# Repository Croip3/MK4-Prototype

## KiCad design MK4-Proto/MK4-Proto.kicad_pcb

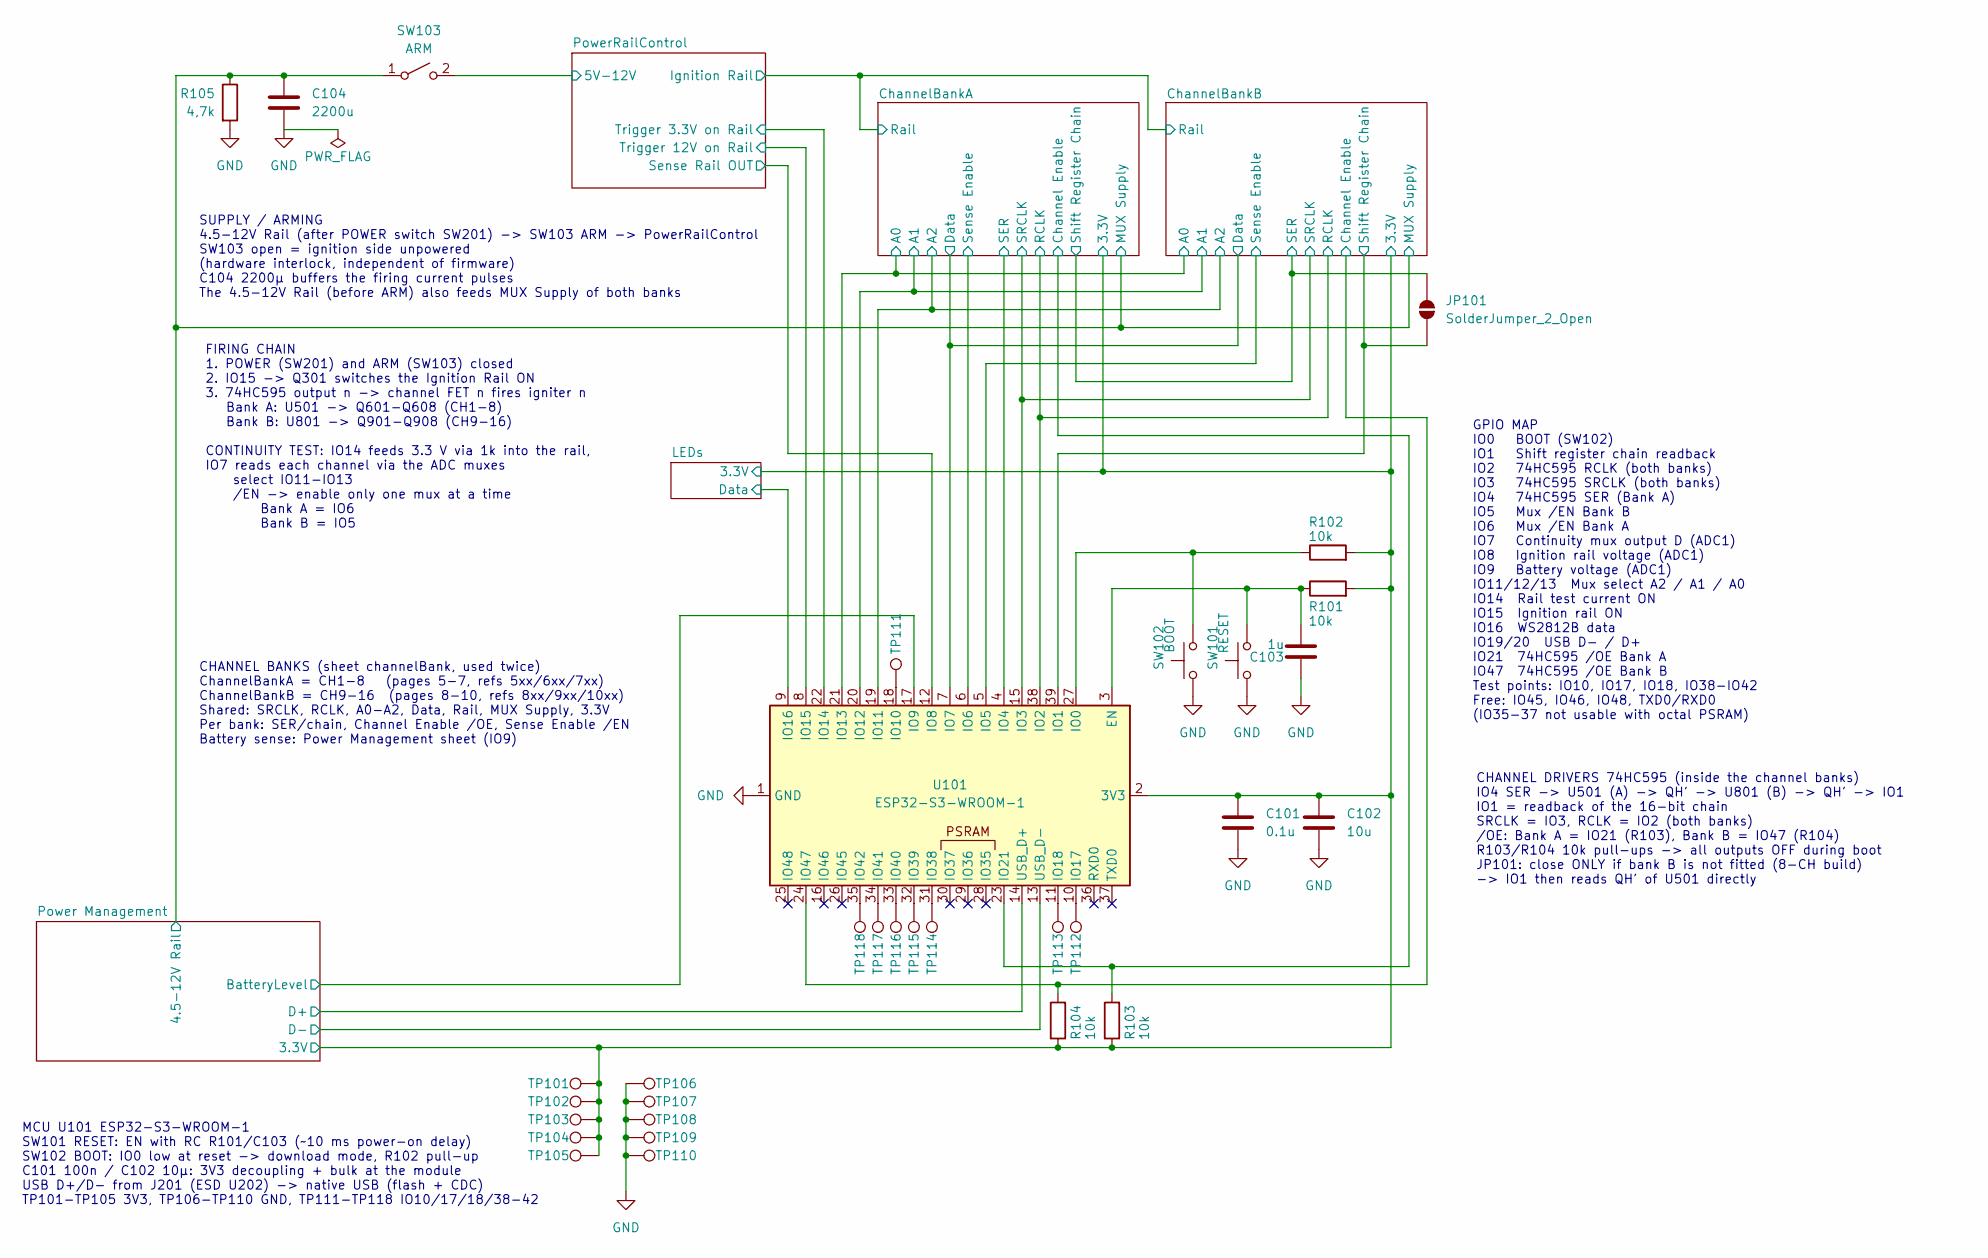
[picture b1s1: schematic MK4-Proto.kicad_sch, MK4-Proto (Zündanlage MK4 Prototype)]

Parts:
C101: 0.1u; C_0805_2012Metric_Pad1.18x1.45mm_HandSolder; LCSC C49678
C102: 10u; C_0805_2012Metric_Pad1.18x1.45mm_HandSolder; LCSC C15850
C103: 1u; C_0805_2012Metric_Pad1.18x1.45mm_HandSolder; LCSC C28323
C104: 2200u; CP_Elec_10x12.6; LCSC C48542923
JP101: SolderJumper_2_Open; SolderJumper-2_P1.3mm_Open_RoundedPad1.0x1.5mm
R101, R102, R103, R104: 10k; R_0603_1608Metric_Pad0.98x0.95mm_HandSolder; LCSC C25804
R105: 4,7k; R_0603_1608Metric_Pad0.98x0.95mm_HandSolder; LCSC C23162
SW101: RESET; SW_PUSH_6mm; LCSC C393938
SW102: BOOT; SW_PUSH_6mm; LCSC C393938
SW103: ARM; SolderWire-0.5sqmm_1x02_P4.6mm_D0.9mm_OD2.1mm
TP101, TP102, TP103, TP104, TP105: 3V3; TestPoint_THTPad_D2.0mm_Drill1.0mm
TP106, TP107, TP108, TP109, TP110: GND; TestPoint_THTPad_D2.0mm_Drill1.0mm
TP111: IO10; TestPoint_THTPad_D2.0mm_Drill1.0mm
TP112: IO17; TestPoint_THTPad_D2.0mm_Drill1.0mm
TP113: IO18; TestPoint_THTPad_D2.0mm_Drill1.0mm
TP114: IO38; TestPoint_THTPad_D2.0mm_Drill1.0mm
TP115: IO39; TestPoint_THTPad_D2.0mm_Drill1.0mm
TP116: IO40; TestPoint_THTPad_D2.0mm_Drill1.0mm
TP117: IO41; TestPoint_THTPad_D2.0mm_Drill1.0mm
TP118: IO42; TestPoint_THTPad_D2.0mm_Drill1.0mm
U101: ESP32-S3-WROOM-1; ESP32-S3-WROOM-1U; LCSC C3013944

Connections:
/ChannelBankA/A0: U101.21 (IO13); also elsewhere on the board
/ChannelBankA/A1: U101.20 (IO12); also elsewhere on the board
/ChannelBankA/A2: U101.19 (IO11); also elsewhere on the board
/ChannelBankA/Channel Enable: R103.2, U101.23 (IO21); also elsewhere on the board
/ChannelBankA/Data: U101.7 (IO7); also elsewhere on the board
/ChannelBankA/MUX Supply: C104.1, R105.1, SW103.1 (A); also elsewhere on the board
/ChannelBankA/RCLK: U101.38 (IO2); also elsewhere on the board
/ChannelBankA/SER: U101.4 (IO4); also elsewhere on the board
/ChannelBankA/SRCLK: U101.15 (IO3); also elsewhere on the board
/ChannelBankA/Sense Enable: U101.6 (IO6); also elsewhere on the board
/ChannelBankA/Shift Register Chain: JP101.2 (B); also elsewhere on the board
/ChannelBankB/Channel Enable: R104.2, U101.24 (IO47); also elsewhere on the board
/ChannelBankB/Sense Enable: U101.5 (IO5); also elsewhere on the board
/ChannelBankB/Shift Register Chain: JP101.1 (A), U101.39 (IO1); also elsewhere on the board
/LEDs/Data: U101.9 (IO16); also elsewhere on the board
/Power Management/BatteryLevel: U101.17 (IO9); also elsewhere on the board
/Power Management/D+: U101.14 (USB_D+); also elsewhere on the board
/Power Management/D-: U101.13 (USB_D-); also elsewhere on the board
/PowerRailControl/5V-12V: SW103.2 (B); also elsewhere on the board
/PowerRailControl/Sense Rail OUT: U101.12 (IO8); also elsewhere on the board
/PowerRailControl/Trigger 3.3V on Rail: U101.22 (IO14); also elsewhere on the board
/PowerRailControl/Trigger 12V on Rail: U101.8 (IO15); also elsewhere on the board
unnamed: C103.2, R101.1, SW101.2, U101.3 (EN)
unnamed: R102.1, SW102.2, U101.27 (IO0)
unnamed: TP111.1 (1_1), U101.18 (IO10)
unnamed: TP112.1 (1_1), U101.10 (IO17)
unnamed: TP113.1 (1_1), U101.11 (IO18)
unnamed: TP114.1 (1_1), U101.31 (IO38)
unnamed: TP115.1 (1_1), U101.32 (IO39)
unnamed: TP116.1 (1_1), U101.33 (IO40)
unnamed: TP117.1 (1_1), U101.34 (IO41)
unnamed: TP118.1 (1_1), U101.35 (IO42)

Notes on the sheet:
SUPPLY / ARMING 4.5-12V Rail (after POWER switch SW201) -> SW103 ARM -> PowerRailControl SW103 open = ignition side unpowered (hardware interlock, independent of firmware) C104 2200µ buffers the firing current pulses The 4.5-12V Rail (before ARM) also feeds MUX Supply of both banks
CHANNEL DRIVERS 74HC595 (inside the channel banks) IO4 SER -> U501 (A) -> QH' -> U801 (B) -> QH' -> IO1 IO1 = readback of the 16-bit chain SRCLK = IO3, RCLK = IO2 (both banks) /OE: Bank A = IO21 (R103), Bank B = IO47 (R104) R103/R104 10k pull-ups -> all outputs OFF during boot JP101: close ONLY if 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
FIRING CHAIN 1. POWER (SW201) and ARM (SW103) closed 2. IO15 -> Q301 switches the Ignition Rail ON 3. 74HC595 output n -> channel FET n fires igniter n Bank A: U501 -> Q601-Q608 (CH1-8) Bank B: U801 -> Q901-Q908 (CH9-16) CONTINUITY TEST: IO14 feeds 3.3 V via 1k into the rail, IO7 reads each channel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
MCU U101 ESP32-S3-WROOM-1 SW101 RESET: EN with RC R101/C103 (~10 ms power-on delay) SW102 BOOT: IO0 low at reset -> download mode, R102 pull-up C101 100n / C102 10µ: 3V3 decoupling + bulk at the module USB D+/D- from J201 (ESD U202) -> native USB (flash + CDC) TP101-TP105 3V3, TP106-TP110 GND, TP11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
GPIO MAP IO0 BOOT (SW102) IO1 Shift register chain readback IO2 74HC595 RCLK (both banks) IO3 74HC595 SRCLK (both banks) IO4 74HC595 SER (Bank A) IO5 Mux /EN Bank B IO6 Mux /EN Bank A IO7 Continuity mux output D (ADC1) IO8 Ignition rail voltage (ADC1) IO9 Battery voltage (ADC1) IO11/12/13 Mux selec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
CHANNEL BANKS (sheet channelBank, used twice) ChannelBankA = CH1-8 (pages 5-7, refs 5xx/6xx/7xx) ChannelBankB = CH9-16 (pages 8-10, refs 8xx/9xx/10xx) Shared: SRCLK, RCLK, A0-A2, Data, Rail, MUX Supply, 3.3V Per bank: SER/chain, Channel Enable /OE, Sense Enable /EN Battery sense: Power Management s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

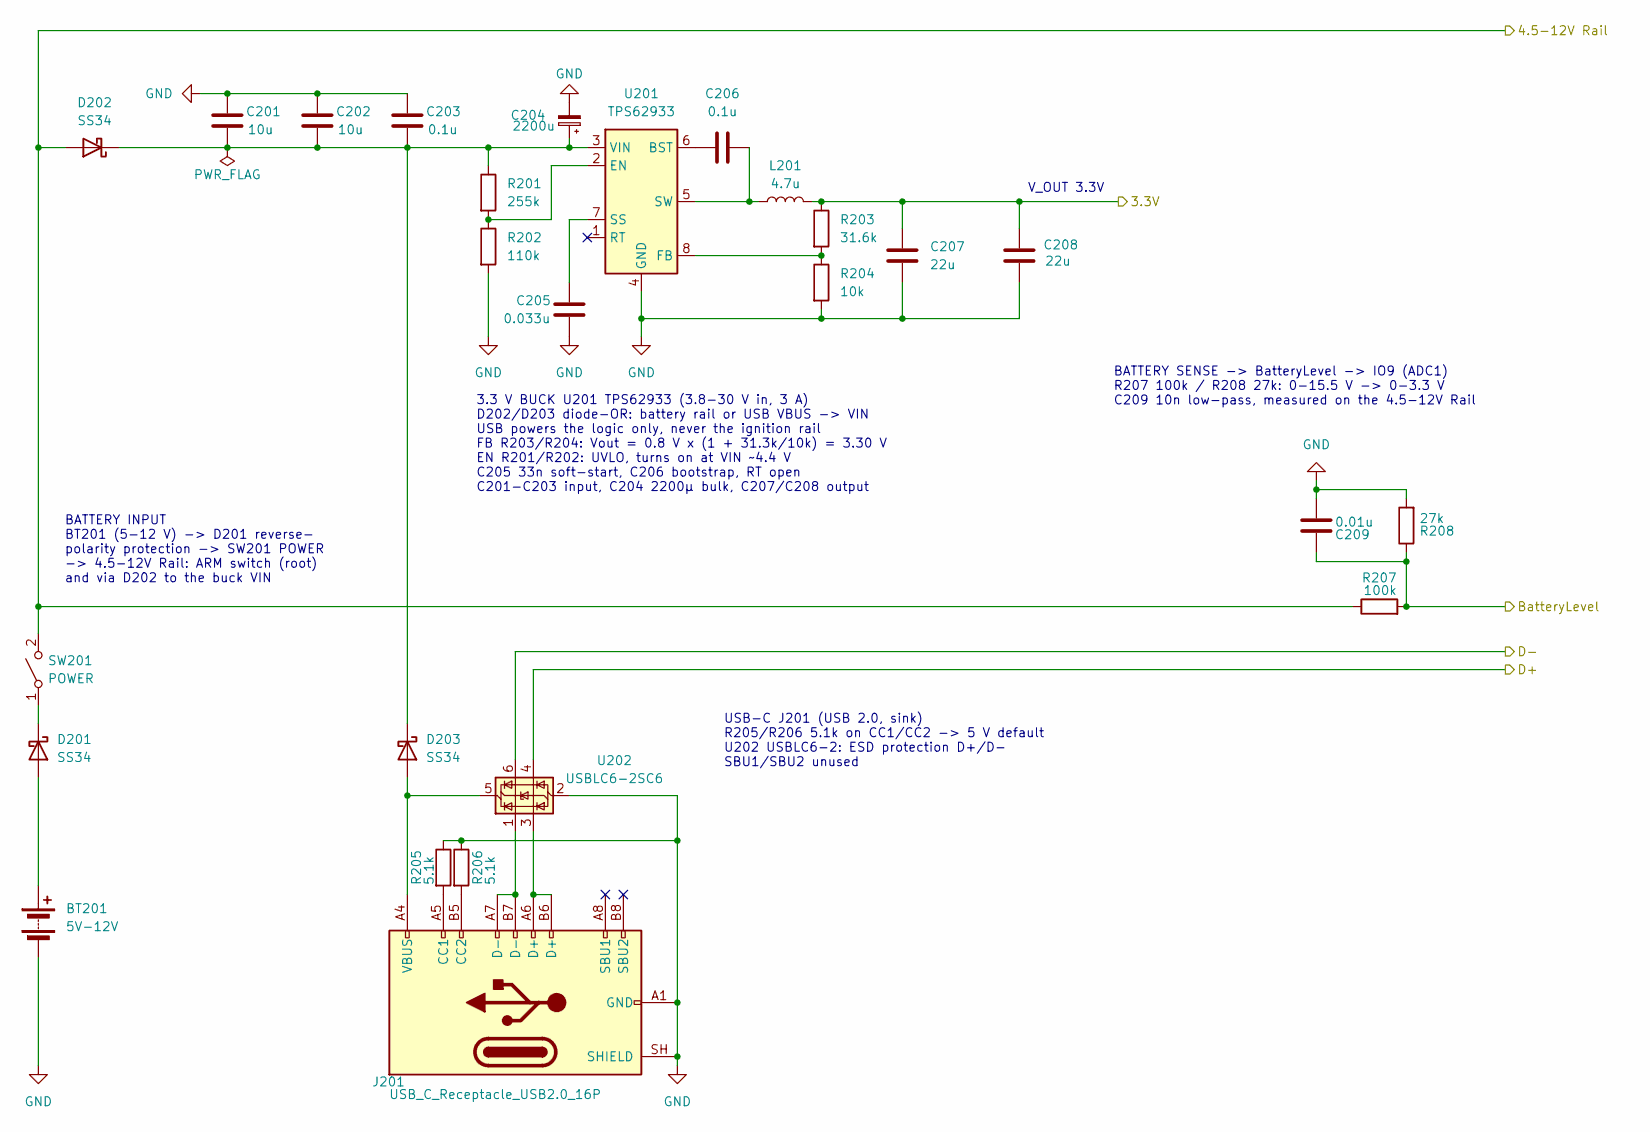
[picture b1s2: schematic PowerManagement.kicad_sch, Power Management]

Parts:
BT201: 5V-12V; SolderWire-0.75sqmm_1x02_P7mm_D1.25mm_OD3.5mm
C201, C202: 10u; C_0805_2012Metric_Pad1.18x1.45mm_HandSolder; LCSC C15850
C203, C206: 0.1u; C_0805_2012Metric_Pad1.18x1.45mm_HandSolder; LCSC C49678
C204: 2200u; CP_Elec_10x12.6; LCSC C48542923
C205: 0.033u; C_0805_2012Metric_Pad1.18x1.45mm_HandSolder; LCSC C1739
C207, C208: 22u; C_0805_2012Metric_Pad1.18x1.45mm_HandSolder; LCSC C45783
C209: 0.01u; C_0805_2012Metric_Pad1.18x1.45mm_HandSolder; LCSC C1710
D201, D202, D203: SS34; D_SMA; LCSC C8678
J201: USB_C_Receptacle_USB2.0_16P; USB_C_Receptacle_GCT_USB4105-xx-A_16P_TopMnt_Horizontal; LCSC C5184243
L201: 4.7u; L_Sunlord_SWPA4030S; LCSC C57269
R201: 255k; R_0603_1608Metric_Pad0.98x0.95mm_HandSolder; LCSC C23354
R202: 110k; R_0603_1608Metric_Pad0.98x0.95mm_HandSolder; LCSC C25805
R203: 31.6k; R_0603_1608Metric_Pad0.98x0.95mm_HandSolder; LCSC C25967
R204: 10k; R_0603_1608Metric_Pad0.98x0.95mm_HandSolder; LCSC C25804
R205, R206: 5.1k; R_0603_1608Metric_Pad0.98x0.95mm_HandSolder; LCSC C23186
R207: 100k; R_0603_1608Metric_Pad0.98x0.95mm_HandSolder; LCSC C25803
R208: 27k; R_0603_1608Metric_Pad0.98x0.95mm_HandSolder; LCSC C22967
SW201: POWER; SolderWire-0.5sqmm_1x02_P4.6mm_D0.9mm_OD2.1mm
U201: TPS62933; SOT-583-8; LCSC C3200405
U202: USBLC6-2SC6; SOT-23-6; LCSC C7519

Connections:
/ChannelBankA/MUX Supply: D202.2 (A), R207.1, SW201.2 (B); also elsewhere on the board
/Power Management/BatteryLevel: C209.2, R207.2, R208.1; also elsewhere on the board
/Power Management/D+: U202.4 (I/O2); also elsewhere on the board
/Power Management/D-: U202.6 (I/O1); also elsewhere on the board
unnamed: BT201.1 (+), D201.2 (A)
unnamed: D201.1 (K), SW201.1 (A)
unnamed: C201.2, C202.2, C203.2, C204.1, D202.1 (K), D203.1 (K), R201.1, U201.3 (VIN)
unnamed: D203.2 (A), J201.A4 (VBUS), J201.A9 (VBUS), J201.B4 (VBUS), J201.B9 (VBUS), U202.5 (VBUS)
unnamed: J201.A5 (CC1), R205.2
unnamed: J201.B5 (CC2), R206.2
unnamed: J201.A6 (D+), J201.B6 (D+), U202.3 (I/O2)
unnamed: J201.A7 (D-), J201.B7 (D-), U202.1 (I/O1)
unnamed: C206.1, U201.6 (BST)
unnamed: R201.2, R202.1, U201.2 (EN)
unnamed: R203.2, R204.1, U201.8 (FB)
unnamed: C205.1, U201.7 (SS)
unnamed: C206.2, L201.1, U201.5 (SW)

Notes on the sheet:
3.3 V BUCK U201 TPS62933 (3.8-30 V in, 3 A) D202/D203 diode-OR: battery rail or USB VBUS -> VIN USB powers the logic only, never the ignition rail FB R203/R204: Vout = 0.8 V x (1 + 31.3k/10k) = 3.30 V EN R201/R202: UVLO, turns on at VIN ~4.4 V C205 33n soft-start, C206 bootstrap, RT open C201-C203 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
USB-C J201 (USB 2.0, sink) R205/R206 5.1k on CC1/CC2 -> 5 V default U202 USBLC6-2: ESD protection D+/D- SBU1/SBU2 unused
V_OUT 3.3V
BATTERY INPUT BT201 (5-12 V) -> D201 reverse- polarity protection -> SW201 POWER -> 4.5-12V Rail: ARM switch (root) and via D202 to the buck VIN
BATTERY SENSE -> BatteryLevel -> IO9 (ADC1) R207 100k / R208 27k: 0-15.5 V -> 0-3.3 V C209 10n low-pass, measured on the 4.5-12V Rail

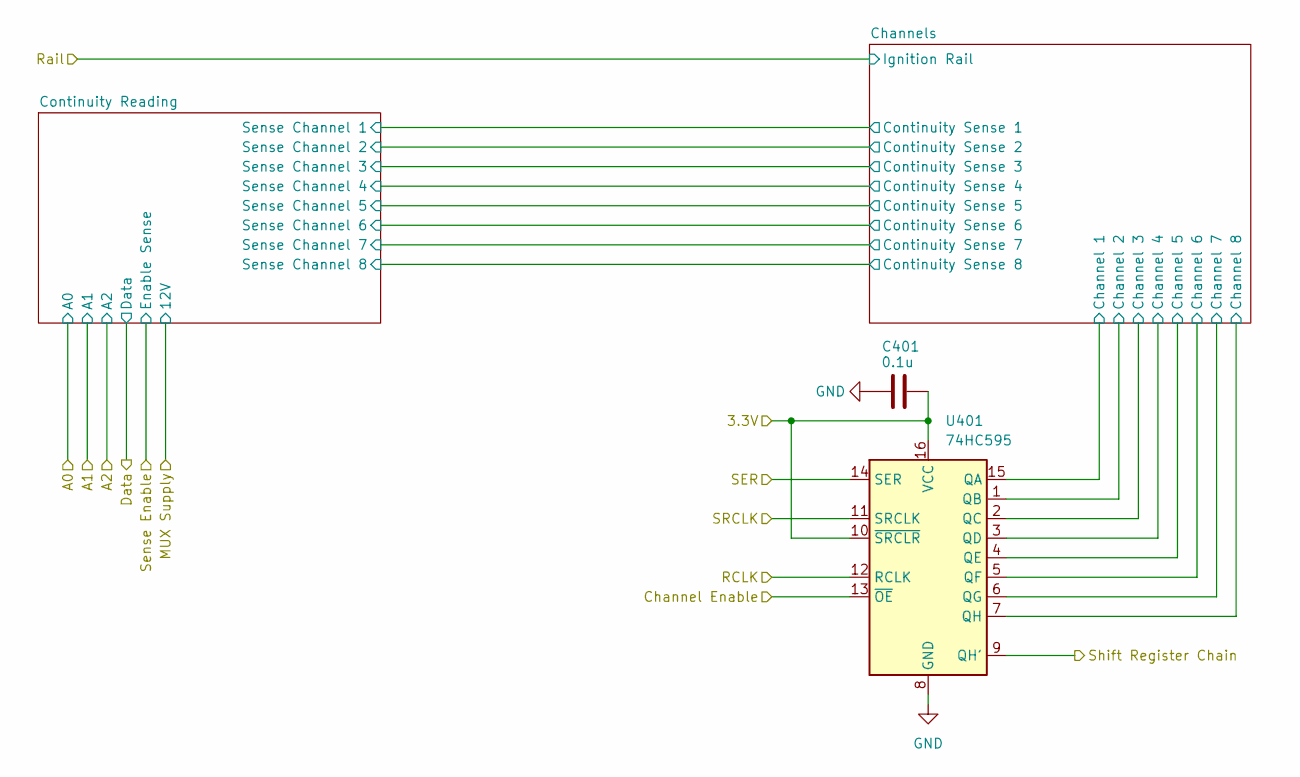
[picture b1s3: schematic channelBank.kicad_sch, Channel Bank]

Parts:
C401: 0.1u; C_0805_2012Metric_Pad1.18x1.45mm_HandSolder
U401: 74HC595; SOIC-16_3.9x9.9mm_P1.27mm

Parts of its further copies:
C801: 0.1u; C_0805_2012Metric_Pad1.18x1.45mm_HandSolder
U801: 74HC595; SOIC-16_3.9x9.9mm_P1.27mm

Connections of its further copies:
/ChannelBankA/RCLK: U801.12 (RCLK); also elsewhere on the board
/ChannelBankA/SRCLK: U801.11 (SRCLK); also elsewhere on the board
/ChannelBankA/Shift Register Chain: U801.14 (SER); also elsewhere on the board
/ChannelBankB/Channel Enable: U801.13 (~OE); also elsewhere on the board
/ChannelBankB/Channels/Channel 1: U801.15 (QA); also elsewhere on the board
/ChannelBankB/Channels/Channel 2: U801.1 (QB); also elsewhere on the board
/ChannelBankB/Channels/Channel 3: U801.2 (QC); also elsewhere on the board
/ChannelBankB/Channels/Channel 4: U801.3 (QD); also elsewhere on the board
/ChannelBankB/Channels/Channel 5: U801.4 (QE); also elsewhere on the board
/ChannelBankB/Channels/Channel 6: U801.5 (QF); also elsewhere on the board
/ChannelBankB/Channels/Channel 7: U801.6 (QG); also elsewhere on the board
/ChannelBankB/Channels/Channel 8: U801.7 (QH); also elsewhere on the board
/ChannelBankB/Shift Register Chain: U801.9 (QH'); also elsewhere on the board

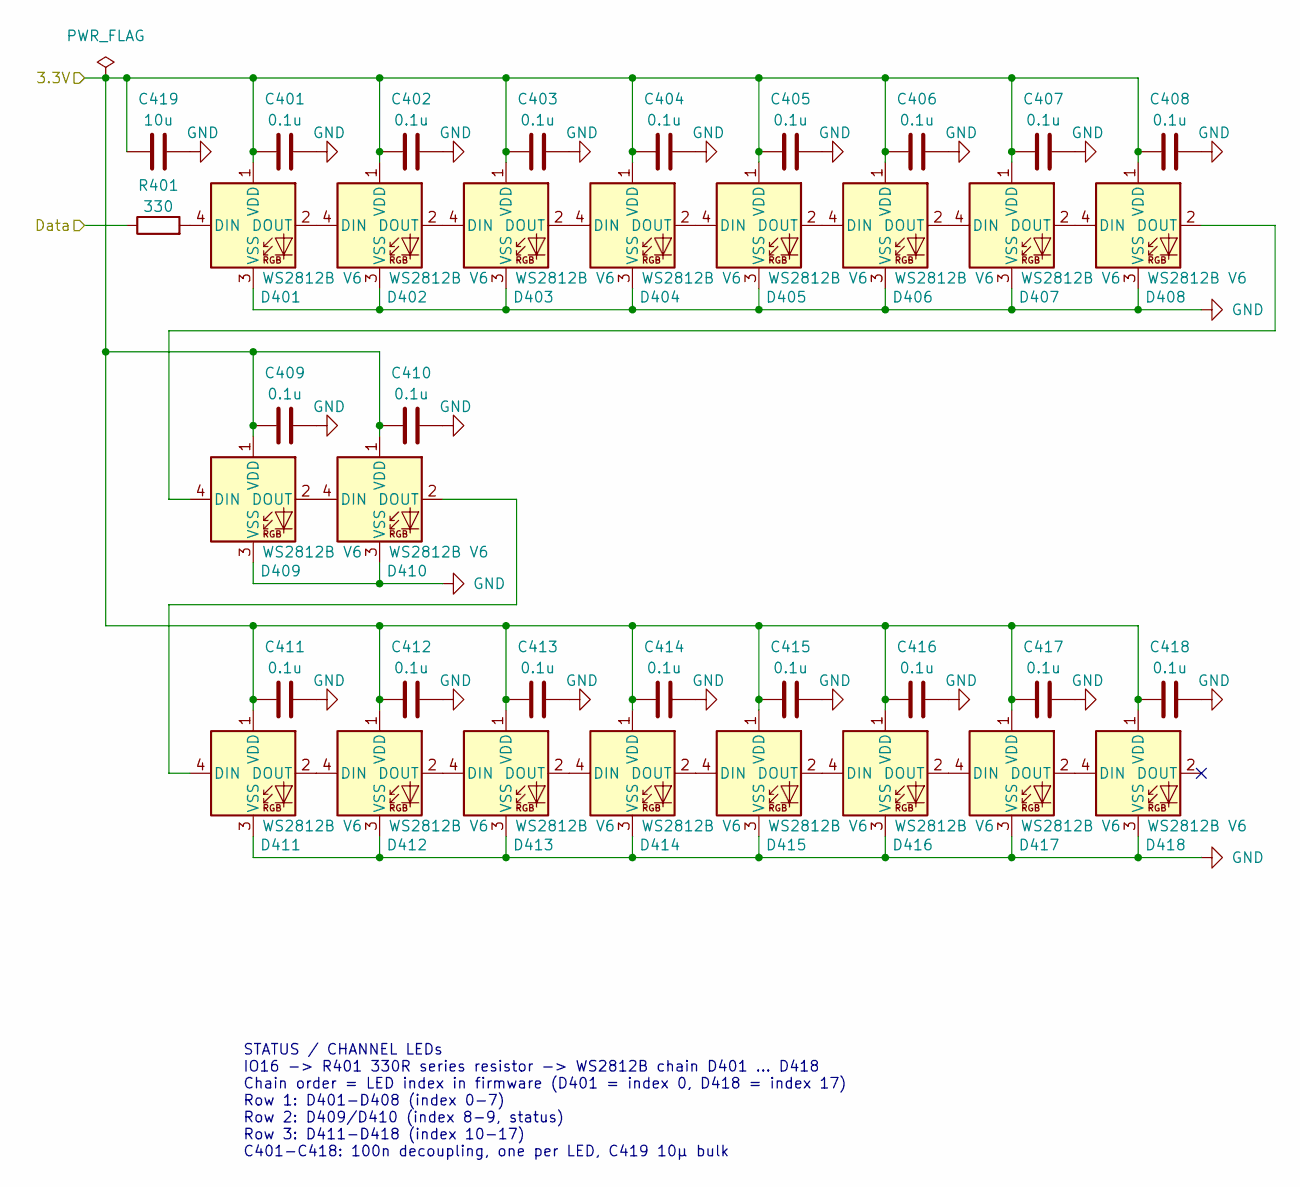
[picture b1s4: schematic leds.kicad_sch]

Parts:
C401, C402, C403, C404, C405, C406, C407, C408, C409, C410, C411, C412, C413, C414, C415, C416, C417, C418: 0.1u; C_0805_2012Metric_Pad1.18x1.45mm_HandSolder; LCSC C49678
C419: 10u; C_0805_2012Metric_Pad1.18x1.45mm_HandSolder; LCSC C15850
D401, D402, D403, D404, D405, D406, D407, D408, D409, D410, D411, D412, D413, D414, D415, D416, D417, D418: WS2812B V6; LED_WS2812B_PLCC4_5.0x5.0mm_P3.2mm; LCSC C52917433
R401: 330; R_0603_1608Metric_Pad0.98x0.95mm_HandSolder; LCSC C23138

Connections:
/LEDs/Data: R401.1; also elsewhere on the board
unnamed: D401.4 (DIN), R401.2
unnamed: D401.2 (DOUT), D402.4 (DIN)
unnamed: D402.2 (DOUT), D403.4 (DIN)
unnamed: D403.2 (DOUT), D404.4 (DIN)
unnamed: D404.2 (DOUT), D405.4 (DIN)
unnamed: D405.2 (DOUT), D406.4 (DIN)
unnamed: D406.2 (DOUT), D407.4 (DIN)
unnamed: D407.2 (DOUT), D408.4 (DIN)
unnamed: D408.2 (DOUT), D409.4 (DIN)
unnamed: D409.2 (DOUT), D410.4 (DIN)
unnamed: D410.2 (DOUT), D411.4 (DIN)
unnamed: D411.2 (DOUT), D412.4 (DIN)
unnamed: D412.2 (DOUT), D413.4 (DIN)
unnamed: D413.2 (DOUT), D414.4 (DIN)
unnamed: D414.2 (DOUT), D415.4 (DIN)
unnamed: D415.2 (DOUT), D416.4 (DIN)
unnamed: D416.2 (DOUT), D417.4 (DIN)
unnamed: D417.2 (DOUT), D418.4 (DIN)

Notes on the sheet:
STATUS / CHANNEL LEDs IO16 -> R401 330R series resistor -> WS2812B chain D401 ... D418 Chain order = LED index in firmware (D401 = index 0, D418 = index 17) Row 1: D401-D408 (index 0-7) Row 2: D409/D410 (index 8-9, status) Row 3: D411-D418 (index 10-17) C401-C418: 100n decoupling, one per LED, C419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

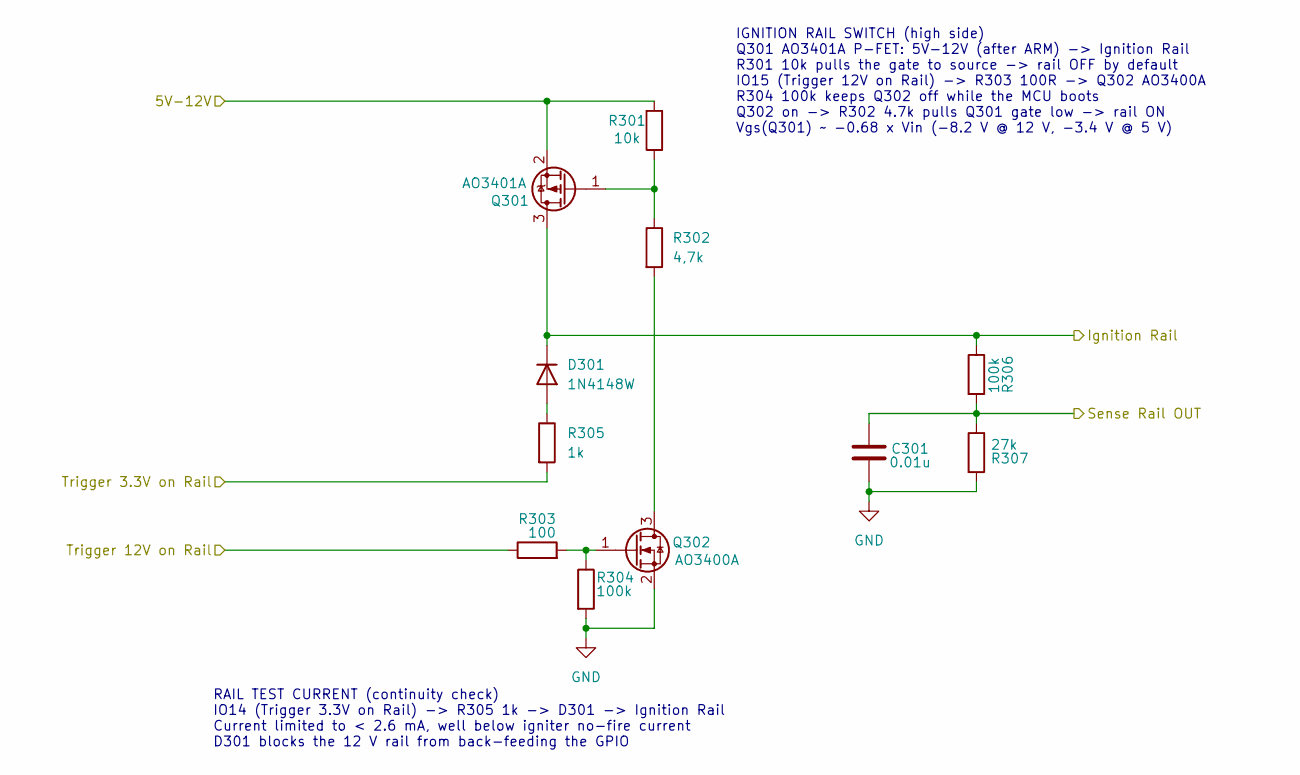
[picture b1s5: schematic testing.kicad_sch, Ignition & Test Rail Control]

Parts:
C301: 0.01u; C_0805_2012Metric_Pad1.18x1.45mm_HandSolder
D301: 1N4148W; D_SOD-123
Q301: AO3401A; SOT-23
Q302: AO3400A; SOT-23
R301: 10k; R_0603_1608Metric_Pad0.98x0.95mm_HandSolder
R302: 4,7k; R_0603_1608Metric_Pad0.98x0.95mm_HandSolder
R303: 100; R_0603_1608Metric_Pad0.98x0.95mm_HandSolder
R304, R306: 100k; R_0603_1608Metric_Pad0.98x0.95mm_HandSolder
R305: 1k; R_0603_1608Metric_Pad0.98x0.95mm_HandSolder
R307: 27k; R_0603_1608Metric_Pad0.98x0.95mm_HandSolder

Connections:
/ChannelBankA/Rail: D301.1 (K), Q301.3 (D), R306.1; also elsewhere on the board
/PowerRailControl/5V-12V: Q301.2 (S), R301.2; also elsewhere on the board
/PowerRailControl/Sense Rail OUT: C301.2, R306.2, R307.1; also elsewhere on the board
/PowerRailControl/Trigger 3.3V on Rail: R305.2; also elsewhere on the board
/PowerRailControl/Trigger 12V on Rail: R303.1; also elsewhere on the board
unnamed: D301.2 (A), R305.1
unnamed: Q301.1 (G), R301.1, R302.1
unnamed: Q302.3 (D), R302.2
unnamed: Q302.1 (G), R303.2, R304.1

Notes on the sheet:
IGNITION RAIL SWITCH (high side) Q301 AO3401A P-FET: 5V-12V (after ARM) -> Ignition Rail R301 10k pulls the gate to source -> rail OFF by default IO15 (Trigger 12V on Rail) -> R303 100R -> Q302 AO3400A R304 100k keeps Q302 off while the MCU boots Q302 on -> R302 4.7k pulls Q301 gate low -> rail ON 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
RAIL TEST CURRENT (continuity check) IO14 (Trigger 3.3V on Rail) -> R305 1k -> D301 -> Ignition Rail Current limited to < 2.6 mA, well below igniter no-fire current D301 blocks the 12 V rail from back-feeding the GPIO

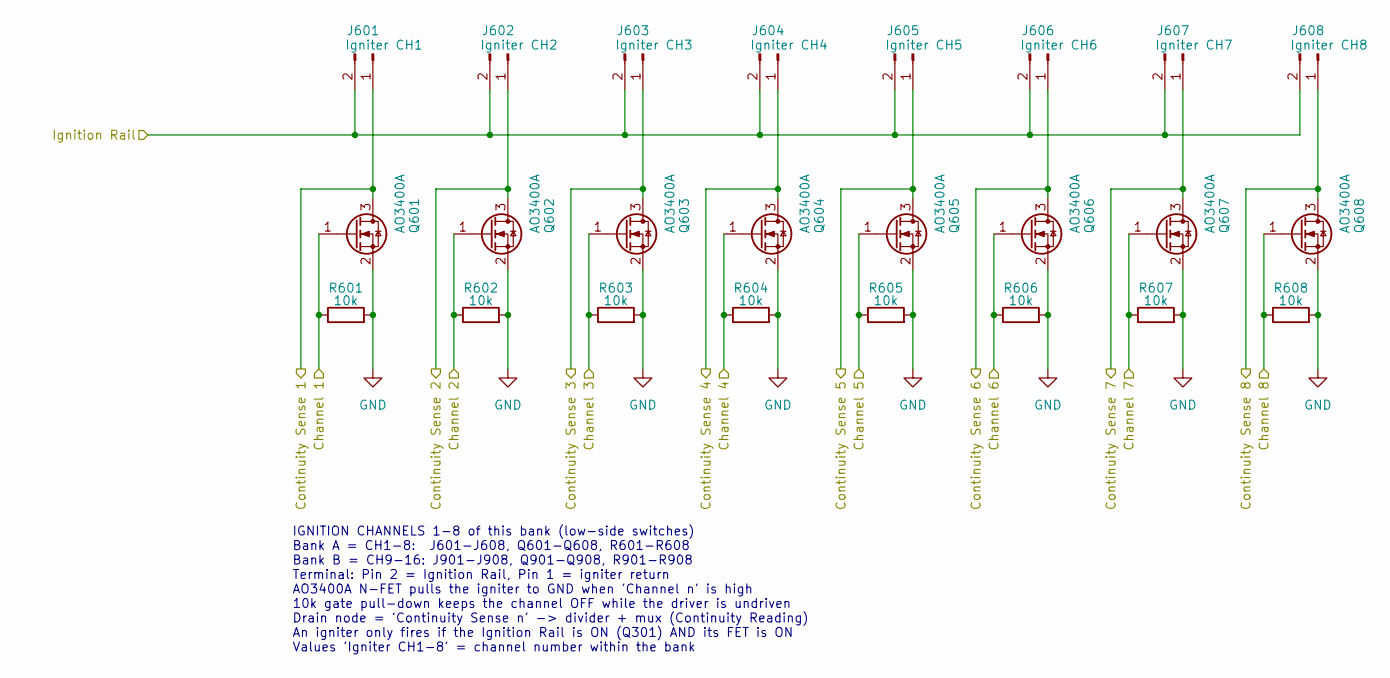
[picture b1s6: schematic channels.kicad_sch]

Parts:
J601: Igniter CH1; CamdenBoss_CTB932VE-2_1x02_P3.81mm_Vertical
J602: Igniter CH2; CamdenBoss_CTB932VE-2_1x02_P3.81mm_Vertical
J603: Igniter CH3; CamdenBoss_CTB932VE-2_1x02_P3.81mm_Vertical
J604: Igniter CH4; CamdenBoss_CTB932VE-2_1x02_P3.81mm_Vertical
J605: Igniter CH5; CamdenBoss_CTB932VE-2_1x02_P3.81mm_Vertical
J606: Igniter CH6; CamdenBoss_CTB932VE-2_1x02_P3.81mm_Vertical
J607: Igniter CH7; CamdenBoss_CTB932VE-2_1x02_P3.81mm_Vertical
J608: Igniter CH8; CamdenBoss_CTB932VE-2_1x02_P3.81mm_Vertical
Q601, Q602, Q603, Q604, Q605, Q606, Q607, Q608: AO3400A; SOT-23; LCSC C20917
R601, R602, R603, R604, R605, R606, R607, R608: 10k; R_0603_1608Metric_Pad0.98x0.95mm_HandSolder; LCSC C25804

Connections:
/ChannelBankA/Channels/Channel 1: Q601.1 (G), R601.1; also elsewhere on the board
/ChannelBankA/Channels/Channel 2: Q602.1 (G), R602.1; also elsewhere on the board
/ChannelBankA/Channels/Channel 3: Q603.1 (G), R603.1; also elsewhere on the board
/ChannelBankA/Channels/Channel 4: Q604.1 (G), R604.1; also elsewhere on the board
/ChannelBankA/Channels/Channel 5: Q605.1 (G), R605.1; also elsewhere on the board
/ChannelBankA/Channels/Channel 6: Q606.1 (G), R606.1; also elsewhere on the board
/ChannelBankA/Channels/Channel 7: Q607.1 (G), R607.1; also elsewhere on the board
/ChannelBankA/Channels/Channel 8: Q608.1 (G), R608.1; also elsewhere on the board
/ChannelBankA/Channels/Continuity Sense 1: J601.1, Q601.3 (D); also elsewhere on the board
/ChannelBankA/Channels/Continuity Sense 2: J602.1, Q602.3 (D); also elsewhere on the board
/ChannelBankA/Channels/Continuity Sense 3: J603.1, Q603.3 (D); also elsewhere on the board
/ChannelBankA/Channels/Continuity Sense 4: J604.1, Q604.3 (D); also elsewhere on the board
/ChannelBankA/Channels/Continuity Sense 5: J605.1, Q605.3 (D); also elsewhere on the board
/ChannelBankA/Channels/Continuity Sense 6: J606.1, Q606.3 (D); also elsewhere on the board
/ChannelBankA/Channels/Continuity Sense 7: J607.1, Q607.3 (D); also elsewhere on the board
/ChannelBankA/Channels/Continuity Sense 8: J608.1, Q608.3 (D); also elsewhere on the board
/ChannelBankA/Rail: J601.2, J602.2, J603.2, J604.2, J605.2, J606.2, J607.2, J608.2; also elsewhere on the board

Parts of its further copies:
J901: Igniter CH1; CamdenBoss_CTB932VE-2_1x02_P3.81mm_Vertical
J902: Igniter CH2; CamdenBoss_CTB932VE-2_1x02_P3.81mm_Vertical
J903: Igniter CH3; CamdenBoss_CTB932VE-2_1x02_P3.81mm_Vertical
J904: Igniter CH4; CamdenBoss_CTB932VE-2_1x02_P3.81mm_Vertical
J905: Igniter CH5; CamdenBoss_CTB932VE-2_1x02_P3.81mm_Vertical
J906: Igniter CH6; CamdenBoss_CTB932VE-2_1x02_P3.81mm_Vertical
J907: Igniter CH7; CamdenBoss_CTB932VE-2_1x02_P3.81mm_Vertical
J908: Igniter CH8; CamdenBoss_CTB932VE-2_1x02_P3.81mm_Vertical
Q901, Q902, Q903, Q904, Q905, Q906, Q907, Q908: AO3400A; SOT-23; LCSC C20917
R901, R902, R903, R904, R905, R906, R907, R908: 10k; R_0603_1608Metric_Pad0.98x0.95mm_HandSolder; LCSC C25804

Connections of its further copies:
/ChannelBankA/Rail: J901.2, J902.2, J903.2, J904.2, J905.2, J906.2, J907.2, J908.2; also elsewhere on the board
/ChannelBankB/Channels/Channel 1: Q901.1 (G), R901.1; also elsewhere on the board
/ChannelBankB/Channels/Channel 2: Q902.1 (G), R902.1; also elsewhere on the board
/ChannelBankB/Channels/Channel 3: Q903.1 (G), R903.1; also elsewhere on the board
/ChannelBankB/Channels/Channel 4: Q904.1 (G), R904.1; also elsewhere on the board
/ChannelBankB/Channels/Channel 5: Q905.1 (G), R905.1; also elsewhere on the board
/ChannelBankB/Channels/Channel 6: Q906.1 (G), R906.1; also elsewhere on the board
/ChannelBankB/Channels/Channel 7: Q907.1 (G), R907.1; also elsewhere on the board
/ChannelBankB/Channels/Channel 8: Q908.1 (G), R908.1; also elsewhere on the board
/ChannelBankB/Channels/Continuity Sense 1: J901.1, Q901.3 (D); also elsewhere on the board
/ChannelBankB/Channels/Continuity Sense 2: J902.1, Q902.3 (D); also elsewhere on the board
/ChannelBankB/Channels/Continuity Sense 3: J903.1, Q903.3 (D); also elsewhere on the board
/ChannelBankB/Channels/Continuity Sense 4: J904.1, Q904.3 (D); also elsewhere on the board
/ChannelBankB/Channels/Continuity Sense 5: J905.1, Q905.3 (D); also elsewhere on the board
/ChannelBankB/Channels/Continuity Sense 6: J906.1, Q906.3 (D); also elsewhere on the board
/ChannelBankB/Channels/Continuity Sense 7: J907.1, Q907.3 (D); also elsewhere on the board
/ChannelBankB/Channels/Continuity Sense 8: J908.1, Q908.3 (D); also elsewhere on the board

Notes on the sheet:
IGNITION CHANNELS 1-8 of this bank (low-side switches) Bank A = CH1-8: J601-J608, Q601-Q608, R601-R608 Bank B = CH9-16: J901-J908, Q901-Q908, R901-R908 Terminal: Pin 2 = Ignition Rail, Pin 1 = igniter return AO3400A N-FET pulls the igniter to GND when 'Channel n' is high 10k gate pull-down keeps th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
